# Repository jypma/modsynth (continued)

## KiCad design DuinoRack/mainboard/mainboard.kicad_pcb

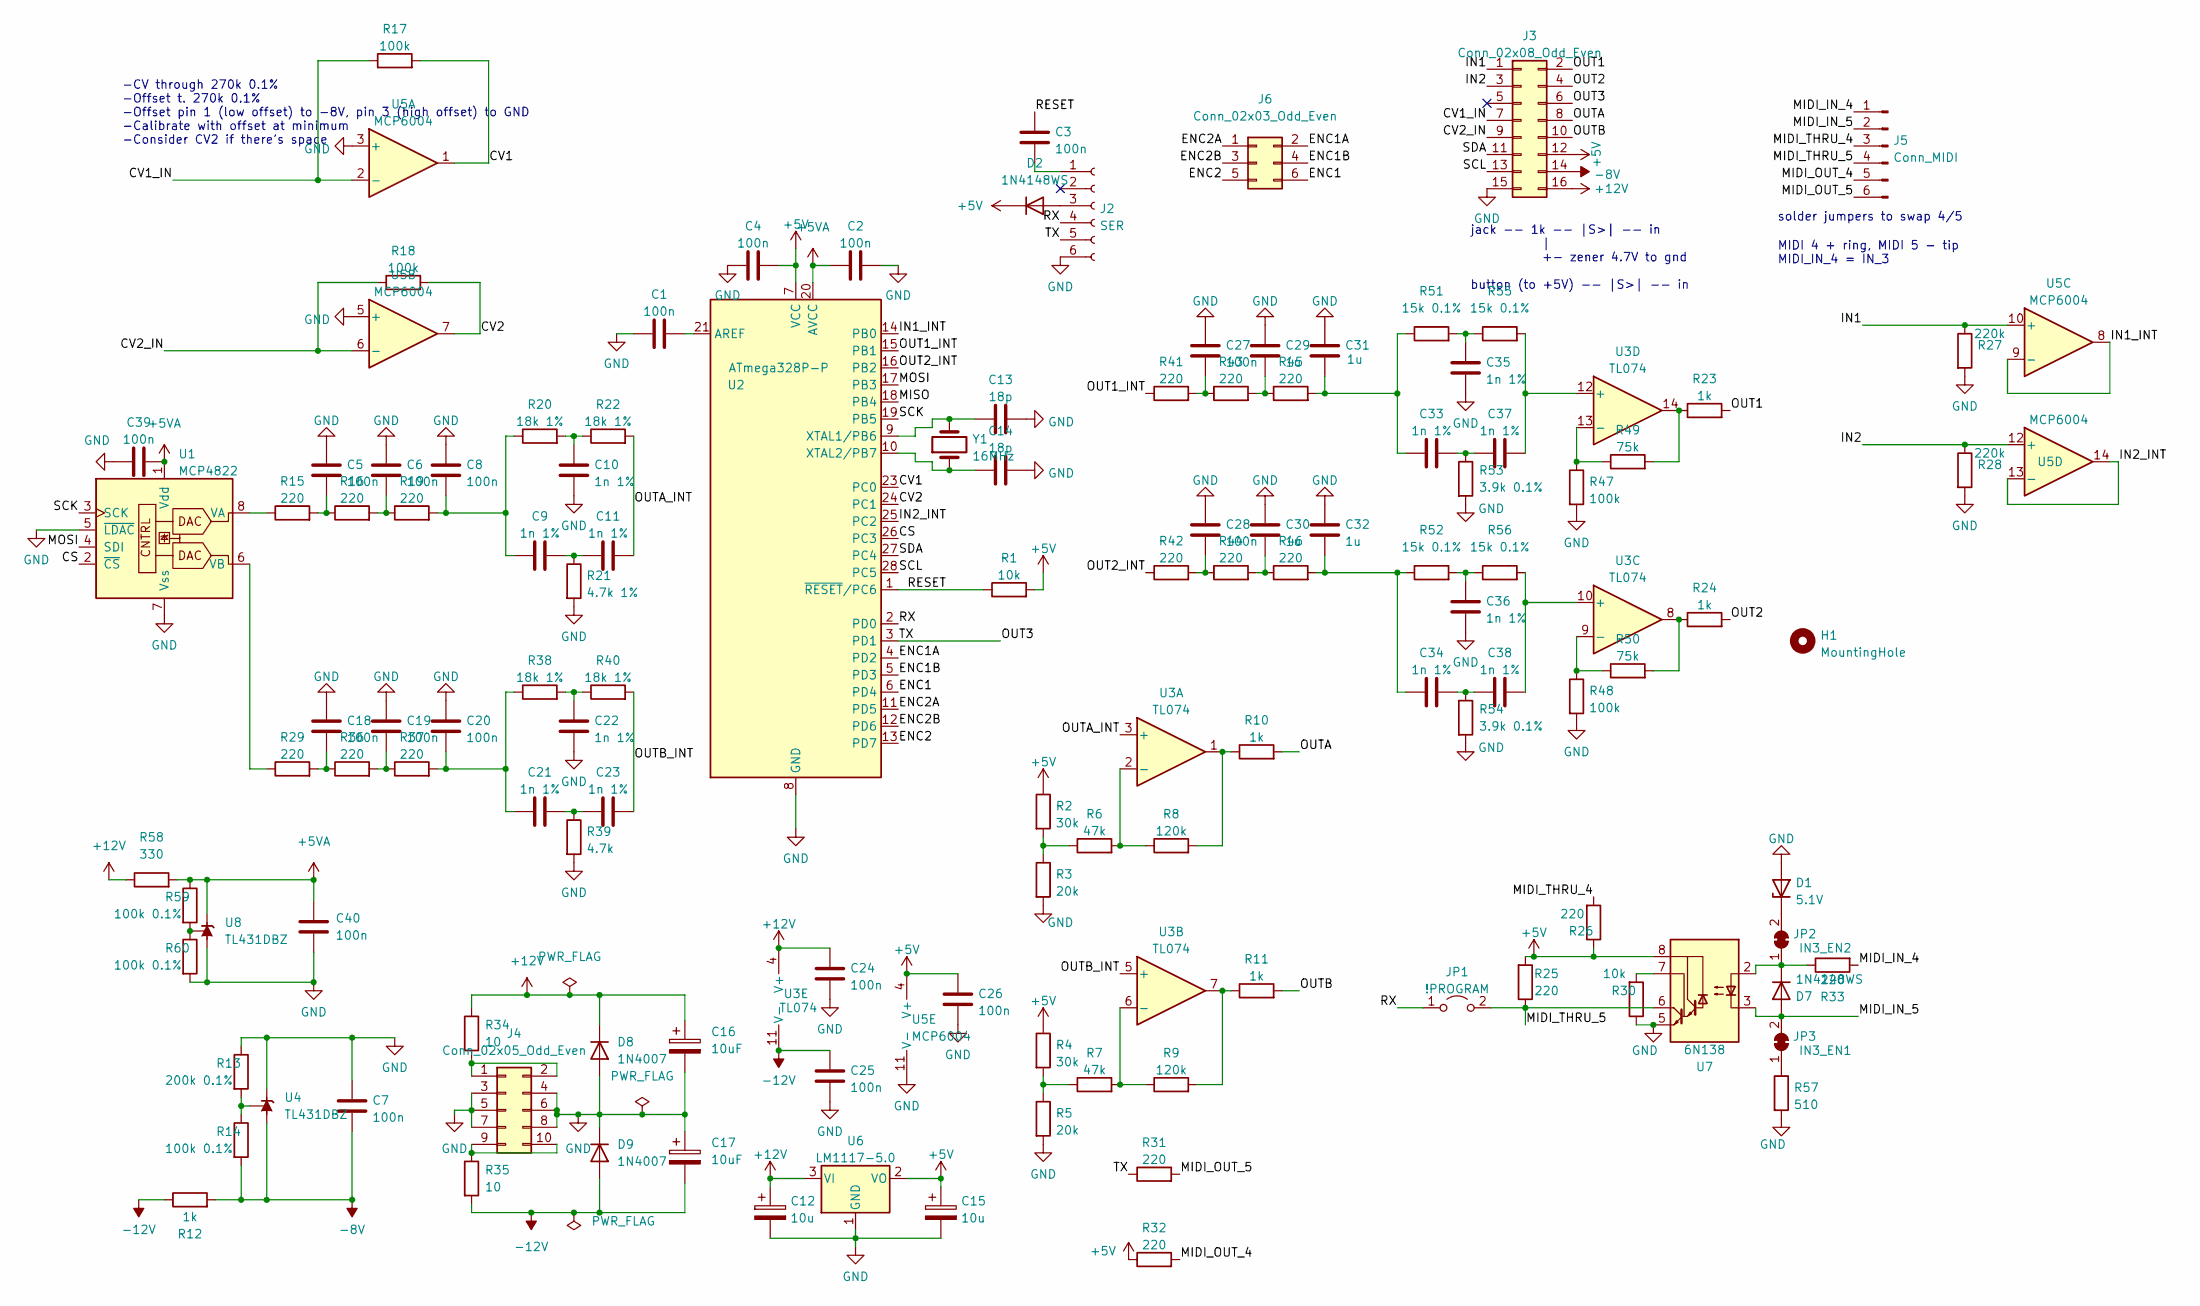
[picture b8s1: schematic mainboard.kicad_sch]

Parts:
C1, C2, C3, C4, C5, C6, C7, C8, C18, C19, C20, C24, C25, C26, C27, C28, C39, C40: 100n; C_0603_1608Metric_Pad1.08x0.95mm_HandSolder
C9, C10, C11, C21, C22, C23, C33, C34, C35, C36, C37, C38: 1n 1%; C_0603_1608Metric_Pad1.08x0.95mm_HandSolder
C12, C15: 10u; C_0603_1608Metric_Pad1.08x0.95mm_HandSolder
C13, C14: 18p; C_0603_1608Metric_Pad1.08x0.95mm_HandSolder
C16, C17: 10uF; CP_Radial_D5.0mm_P2.50mm
C29, C30, C31, C32: 1u; C_0603_1608Metric_Pad1.08x0.95mm_HandSolder
D1: 5.1V; D_DO-35_SOD27_P2.54mm_Vertical_AnodeUp
D2, D7: 1N4148WS; D_SOD-323_HandSoldering
D8, D9: 1N4007; D_DO-41_SOD81_P7.62mm_Horizontal
H1: MountingHole; MountingHole_3.2mm_M3_DIN965
J2: SER; PinHeader_1x06_P2.54mm_Vertical
J3: Conn_02x08_Odd_Even; PinHeader_2x08_P2.54mm_Vertical
J4: Conn_02x05_Odd_Even; PinHeader_2x05_P2.54mm_Vertical
J5: Conn_MIDI; PinHeader_1x06_P2.54mm_Vertical
J6: Conn_02x03_Odd_Even; PinHeader_2x03_P2.54mm_Vertical
JP1: !PROGRAM; PinHeader_1x02_P2.54mm_Vertical
JP2: IN3_EN2; SolderJumper-2_P1.3mm_Bridged_RoundedPad1.0x1.5mm
JP3: IN3_EN1; SolderJumper-2_P1.3mm_Bridged_RoundedPad1.0x1.5mm
R1, R30: 10k; R_0603_1608Metric_Pad0.98x0.95mm_HandSolder
R2, R4: 30k; R_0603_1608Metric_Pad0.98x0.95mm_HandSolder
R3, R5: 20k; R_0603_1608Metric_Pad0.98x0.95mm_HandSolder
R6, R7: 47k; R_0603_1608Metric_Pad0.98x0.95mm_HandSolder
R8, R9: 120k; R_0603_1608Metric_Pad0.98x0.95mm_HandSolder
R10, R11, R12, R23, R24: 1k; R_0603_1608Metric_Pad0.98x0.95mm_HandSolder
R13: 200k 0.1%; R_0603_1608Metric_Pad0.98x0.95mm_HandSolder
R14, R59, R60: 100k 0.1%; R_0603_1608Metric_Pad0.98x0.95mm_HandSolder
R15, R16, R19, R25, R26, R29, R31, R32, R33, R36, R37, R41, R42, R43, R44, R45, R46: 220; R_0603_1608Metric_Pad0.98x0.95mm_HandSolder
R17, R18, R47, R48: 100k; R_0603_1608Metric_Pad0.98x0.95mm_HandSolder
R20, R22, R38, R40: 18k 1%; R_0603_1608Metric_Pad0.98x0.95mm_HandSolder
R21: 4.7k 1%; R_0603_1608Metric_Pad0.98x0.95mm_HandSolder
R27, R28: 220k; R_0603_1608Metric_Pad0.98x0.95mm_HandSolder
R34, R35: 10; R_0603_1608Metric_Pad0.98x0.95mm_HandSolder
R39: 4.7k; R_0603_1608Metric_Pad0.98x0.95mm_HandSolder
R49, R50: 75k; R_0603_1608Metric_Pad0.98x0.95mm_HandSolder
R51, R52, R55, R56: 15k 0.1%; R_0603_1608Metric_Pad0.98x0.95mm_HandSolder
R53, R54: 3.9k 0.1%; R_0603_1608Metric_Pad0.98x0.95mm_HandSolder
R57: 510; R_0603_1608Metric_Pad0.98x0.95mm_HandSolder
R58: 330; R_0603_1608Metric_Pad0.98x0.95mm_HandSolder
U1: MCP4822; DIP-8_W7.62mm_Socket
U2: ATmega328P-P; DIP-28_W7.62mm_Socket
U3: TL074; SO-14_3.9x8.65mm_P1.27mm
U4, U8: TL431DBZ; SOT-23
U5: MCP6004; SO-14_3.9x8.65mm_P1.27mm
U6: LM1117-5.0; SOT-223
U7: 6N138; DIP-8_W7.62mm_Socket
Y1: 16MHz; Crystal_HC18-U_Vertical

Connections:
+5V: C4.2, C15.1, C26.1, D2.1 (K), J3.12, R1.2, R2.1, R4.1, R25.2, R26.1, R32.1, U2.7 (VCC), U5.4 (V+), U6.2 (VO), U7.8 (VCC)
+5VA: C2.1, C39.2, C40.1, R58.2, R59.1, U1.1 (Vdd), U2.20 (AVCC), U8.1 (K)
+12V: C12.1, C16.1, C24.1, D8.1 (K), J3.16, R34.1, R58.1, U3.4 (V+), U6.3 (VI)
-8V: C7.2, J3.14, R12.2, R14.2, U4.3 (A)
-12V: C17.2, C25.1, D9.2 (A), R12.1, R35.2, U3.11 (V-)
/CS: U1.2 (~CS), U2.26 (PC3)
/CV1: R17.2, U2.23 (PC0), U5.1
/CV1_IN: J3.7, R17.1, U5.2 (-)
/CV2: R18.2, U2.24 (PC1), U5.7
/CV2_IN: J3.9, R18.1, U5.6 (-)
/ENC1: J6.6, U2.6 (PD4)
/ENC1A: J6.2, U2.4 (PD2)
/ENC1B: J6.4, U2.5 (PD3)
/ENC2: J6.5, U2.13 (PD7)
/ENC2A: J6.1, U2.11 (PD5)
/ENC2B: J6.3, U2.12 (PD6)
/IN1: J3.1, R27.1, U5.10 (+)
/IN1_INT: U2.14 (PB0), U5.8, U5.9 (-)
/IN2: J3.3, R28.1, U5.12 (+)
/IN2_INT: U2.25 (PC2), U5.13 (-), U5.14
/MIDI_IN_4: J5.1, R33.2
/MIDI_IN_5: D7.2 (A), J5.2, JP3.2 (B), U7.3 (C2)
/MIDI_OUT_4: J5.5, R32.2
/MIDI_OUT_5: J5.6, R31.2
/MIDI_THRU_4: J5.3, R26.2
/MIDI_THRU_5: J5.4, JP1.2 (B), R25.1, U7.6 (VO2)
/MISO: U2.18 (PB4)
/MOSI: U1.4 (SDI), U2.17 (PB3)
/OUT1: J3.2, R23.2
/OUT1_INT: R41.1, U2.15 (PB1)
/OUT2: J3.4, R24.2
/OUT2_INT: R42.1, U2.16 (PB2)
/OUT3: J2.5, J3.6, R31.1, U2.3 (PD1)
/OUTA: J3.8, R10.2
/OUTA_INT: C11.2, R22.2, U3.3 (+)
/OUTB: J3.10, R11.2
/OUTB_INT: C23.2, R40.2, U3.5 (+)
/RESET: C3.1, R1.1, U2.1 (~RESET/PC6)
/RX: J2.4, JP1.1 (A), U2.2 (PD0)
/SCK: U1.3 (SCK), U2.19 (PB5)
/SCL: J3.13, U2.28 (PC5)
/SDA: J3.11, U2.27 (PC4)
GND: C1.1, C2.2, C4.1, C5.1, C6.1, C7.1, C8.1, C10.2, C12.2, C13.2, C14.2, C15.2, C16.2, C17.1, C18.1, C19.1, C20.1, C22.2, C24.2, C25.2, C26.2, C27.1, C28.1, C29.1, C30.1, C31.1, C32.1, C35.2, C36.2, C39.1, C40.2, D1.2 (A), D8.2 (A), D9.1 (K), J2.6, J3.15, J4.3, J4.4, J4.5, J4.6, J4.7, J4.8, R3.2, R5.2, R13.1, R21.2, R27.2, R28.2, R30.1, R39.2, R47.2, R48.2, R53.2, R54.2, R57.2, R60.2, U1.5 (~LDAC), U1.7 (Vss), U2.8 (GND), U2.22 (GND), U4.1 (K), U5.3 (+), U5.5 (+), U5.11 (V-), U6.1 (GND), U7.5 (GND), U8.3 (A)
unnamed: C1.2, U2.21 (AREF)
unnamed: C3.2, J2.1
unnamed: C5.2, R15.2, R16.1
unnamed: C6.2, R16.2, R19.1
unnamed: C8.2, C9.1, R19.2, R20.1
unnamed: C10.1, R20.2, R22.1
unnamed: C9.2, C11.1, R21.1
unnamed: C13.1, U2.9 (XTAL1/PB6), Y1.2
unnamed: C14.1, U2.10 (XTAL2/PB7), Y1.1
unnamed: C18.2, R29.2, R36.1
unnamed: C19.2, R36.2, R37.1
unnamed: C20.2, C21.1, R37.2, R38.1
unnamed: C21.2, C23.1, R39.1
unnamed: C22.1, R38.2, R40.1
unnamed: C27.2, R41.2, R43.1
unnamed: C28.2, R42.2, R44.1
unnamed: C29.2, R43.2, R45.1
unnamed: C30.2, R44.2, R46.1
unnamed: C31.2, C33.1, R45.2, R51.1
unnamed: C32.2, C34.1, R46.2, R52.1
unnamed: C33.2, C37.1, R53.1
unnamed: C34.2, C38.1, R54.1
unnamed: C35.1, R51.2, R55.1
unnamed: C36.1, R52.2, R56.1
unnamed: C37.2, R55.2, U3.12 (+)
unnamed: C38.2, R56.2, U3.10 (+)
unnamed: D1.1 (K), JP2.2 (B)
unnamed: D7.1 (K), JP2.1 (A), R33.1, U7.2 (C1)
unnamed: D2.2 (A), J2.3
unnamed: J4.1, J4.2, R34.2
unnamed: J4.9, J4.10, R35.1
unnamed: JP3.1 (A), R57.1
unnamed: R2.2, R3.1, R6.1
unnamed: R4.2, R5.1, R7.1
unnamed: R6.2, R8.1, U3.2 (-)
unnamed: R7.2, R9.1, U3.6 (-)
unnamed: R8.2, R10.1, U3.1
unnamed: R9.2, R11.1, U3.7
unnamed: R13.2, R14.1, U4.2 (REF)
unnamed: R15.1, U1.8 (VA)
unnamed: R23.1, R49.2, U3.14
unnamed: R24.1, R50.2, U3.8
unnamed: R29.1, U1.6 (VB)
unnamed: R30.2, U7.7 (VO1)
unnamed: R47.1, R49.1, U3.13 (-)
unnamed: R48.1, R50.1, U3.9 (-)
unnamed: R59.2, R60.1, U8.2 (REF)

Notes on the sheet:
solder jumpers to swap 4/5
jack -- 1k -- |S>| -- in | +- zener 4.7V to gnd button (to +5V) -- |S>| -- in
-CV through 270k 0.1% -Offset t. 270k 0.1% -Offset pin 1 (low offset) to -8V, pin 3 (high offset) to GND -Calibrate with offset at minimum -Consider CV2 if there's space
MIDI 4 + ring, MIDI 5 - tip MIDI_IN_4 = IN_3

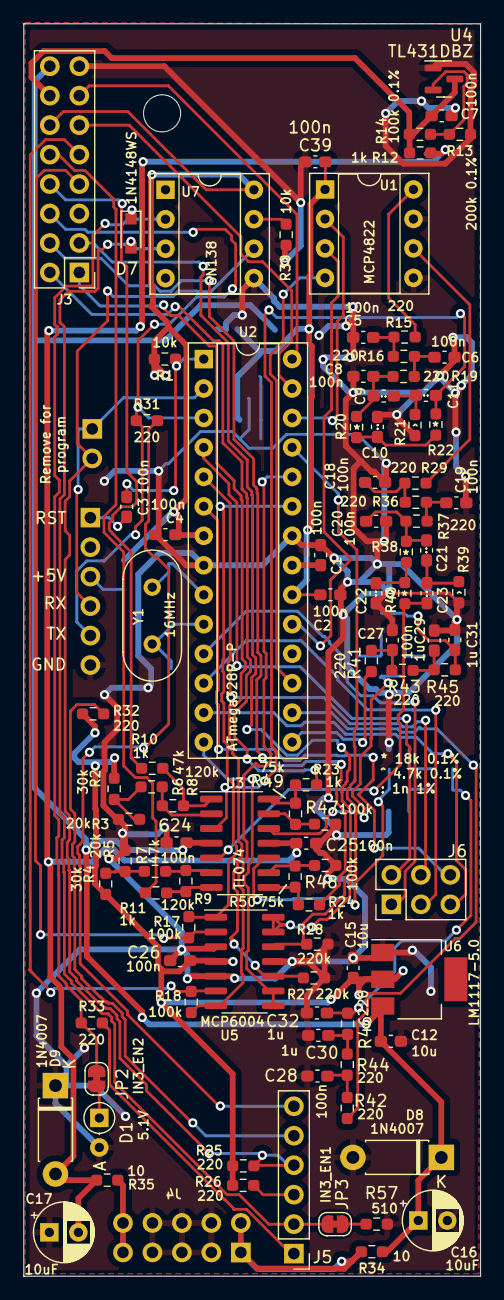
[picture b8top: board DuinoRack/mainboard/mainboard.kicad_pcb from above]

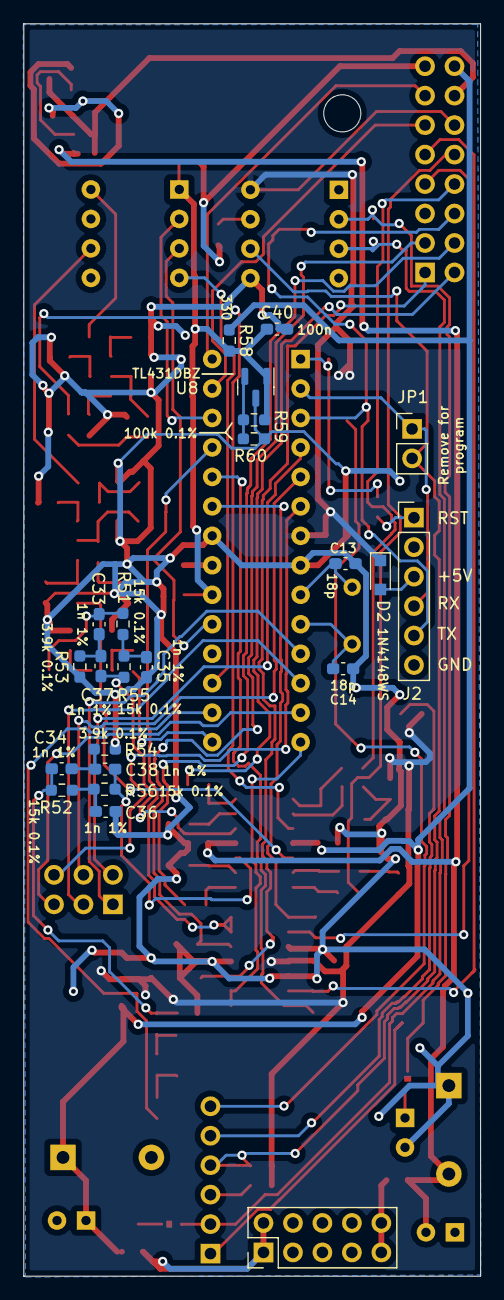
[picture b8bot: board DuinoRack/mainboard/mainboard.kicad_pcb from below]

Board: 2 copper layers, 39.4 x 107.9 mm, 123 parts (23 on the bottom side), 89 nets.

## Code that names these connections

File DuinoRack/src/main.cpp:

#include "Arduino.h"
#include "MCP_DAC.h"
#include <lcdgfx.h>
#include <Versatile_RotaryEncoder.h>
#include "Module.h"
#include "OutputBuf.h"
#include "FuncGen.h"
#include "Calibrate.h"
#include "ADSR.hpp"
#include "IO.h"
#include "LFO.hpp"
#include "Quantize.h"
#include "MIDIMod.h"
#include "canvas/canvas.h"
#include "pins_arduino.h"
#include "Storage.hpp"
#include "Debug.hpp"
#include "Random.hpp"
#include "Sequencer.hpp"

//#define TIMING

// display: 300 bytes RAM

Module currentMod = LFO::module;//FuncGen::module;
uint8_t currentModIdx = 3;

uint8_t shownModIdx = currentModIdx;
uint8_t currentControlIdx = 0;

// Encoder 1 is "Select"
auto encoder1 = Versatile_RotaryEncoder(2,3,4); // PD2, PD3, PD4
// Encoder 2 is "Adjust"
auto encoder2 = Versatile_RotaryEncoder(5,6,7); // PD5, PD6, PD7

OutputBuf::Buffer a, b;
OutputBuf::Buffer *current = &b;

DisplaySSD1306_128x64_I2C display(-1);

MCP4821 MCP;
uint16_t bufferCount;
uint32_t lastTime = 0;
uint8_t oldOverruns = 0;

void fillBuffer() {
  if (OutputBuf::needNextBuffer()) {
    current = (current == &a) ? &b : &a;
    bufferCount++;
#ifdef TIMING
    PORTD |= (1 << 3);
#endif
    currentMod.fillBuffer(*current);  // On arduino boot: ~500us
#ifdef TIMING
    PORTD &= ~(1 << 3);
#endif
    OutputBuf::setNextBuffer(current);
  } else if (encoder1.ReadEncoder()) {
    debugSerial("E1");
  } else if (encoder2.ReadEncoder()) {
    debugSerial("E2");
  } else {
    IO::readIfNeeded();
  }
}

ISR(TIMER2_COMPA_vect) {
#ifdef TIMING
  PORTD |= (1 << 2);
#endif
  OutputBuf::advance();
#ifdef TIMING
  PORTD &= ~(1 << 2);
#endif
}

void setModuleIdx(int8_t idx) {
  currentMod.stop();
  currentControlIdx = 0;
  currentModIdx = idx % MODULE_COUNT;
  debugSerial(currentModIdx);
  switch(currentModIdx) {
    case 0: currentMod = FuncGen::module; break;
    case 1: currentMod = ADSR::module; break;
    case 2: currentMod = MIDIMod::module; break;
    case 3: currentMod = LFO::module; break;
    case 4: currentMod = Quantize::module; break;
    case 5: currentMod = Sequencer::module; break;
    default: currentMod = Calibrate::module;
  }
  // Startup trigger
  currentMod.start();
  currentMod.adjust(0);
}

void drawText(uint8_t x, uint8_t y, const char *s) {
  if (!*s) return;
  display.setTextCursor(x, y);
  while (*s) {
    fillBuffer();
    display.printChar(*s);
    fillBuffer();
    s++;
  }
}

void drawSelected(uint8_t x, uint8_t y, uint8_t control) {
  drawChar(x, y, (currentControlIdx == control) ? '>' : ' ');
}

void drawChar(uint8_t x, uint8_t y, char ch) {
  if (!ch) return;
  display.setTextCursor(x, y);
  fillBuffer();
  display.printChar(ch);
}

void clearChars(uint8_t x, uint8_t y, uint8_t count) {
  display.setTextCursor(x, y);
  while (count > 0) {
    fillBuffer();
    display.printChar(' ');
    count--;
  }
}

void drawDecimal(uint8_t x, uint8_t y, int16_t value) {
  char str[7];
  itoa(value, str, 10);
  drawText(x, y, str);
  drawTextPgm(x + strlen(str) * 6, y, clear);
}

void drawDecimal(uint8_t x, uint8_t y, int16_t value, uint8_t expectedChars) {
  char str[7];
  itoa(value, str, 10);
  drawText(x, y, str);
  uint8_t len = strlen(str);
  clearChars(x + len * 6, y, (expectedChars > len) ? expectedChars - len : 0);
}

void drawDecimal(uint8_t x, uint8_t y, int16_t value, char suffix, uint8_t expectedChars) {
  char str[7];
  itoa(value, str, 10);
  drawText(x, y, str);
  uint8_t len = strlen(str);
  drawChar(x + len * 6, y, suffix);
  len++;
  clearChars(x + len * 6, y, (expectedChars > len) ? expectedChars - len : 0);
}

void drawTextPgm(uint8_t x, uint8_t y, const char *s) {
  uint8_t ch = pgm_read_byte(s);
  if (!ch) return;
  display.setTextCursor(x, y);
  while (ch) {
    fillBuffer();
    display.printChar(ch);
    fillBuffer();
    s++;
    ch = pgm_read_byte(s);
  }
}

bool showLongPress = false;
void showModule() {
  if (shownModIdx != currentModIdx) {
    display.fill(0x00);
  }
  if (currentControlIdx == 0) {
    drawText(0, 8, ">");
  } else {
    drawText(0, 8, " ");
  }
  drawText(120, 8, showLongPress ? "S" : " ");
  drawTextPgm(8, 8, currentMod.name);
  shownModIdx = currentModIdx;
}

// Encoder 2 is "Adjust"
void handleEncoder2Rotate(int8_t rotation) {
  static uint32_t prevTime = 0;
  static uint8_t accel = 1;
  auto time = millis();
  uint8_t maxAccel = (currentControlIdx == 0) ? 1 : 16;
  if ((time - prevTime < 100) && (accel < maxAccel)) {
    accel <<= 1;
  } else {
    accel = 1;
  }
  prevTime = time;

  // Don't draw to screen here, as this may be called in the middle of drawing to the screen!
  if (currentControlIdx == 0) {
    setModuleIdx(applyDelta<uint8_t>(currentModIdx, rotation, 0, MODULE_COUNT - 1));
  } else {
    // TODO control acceleration differently for different controls
    rotation *= accel;
    currentMod.adjust(rotation);
  }
}

void handleEncoder2PressRelease() {
  showLongPress = false;
  if (currentMod.adjustPressed != NULL) {
    currentMod.adjustPressed();
  }
}

// Encoder 1 is "Select"
void handleEncoder1Rotate(int8_t rotation) {
  static uint32_t prevTime = 0;
  static uint8_t accel = 1;
  auto time = millis();
  uint8_t maxAccel = 4;
  if ((time - prevTime < 100) && (accel < maxAccel)) {
    accel <<= 1;
  } else {
    accel = 1;
  }
  prevTime = time;
  rotation *= accel;

  // Don't draw to screen here, as this may be called in the middle of drawing to the screen!
  currentControlIdx = (currentControlIdx + (currentMod.controlCount + 1) + rotation) % (currentMod.controlCount + 1);
}


void handleEncoder1LongPress() {
  showLongPress = true;
}

void handleEncoder1LongPressRelease() {
  // TODO: Show a menu here to load/save preset slots. For now, we just save in preset 0.
  Storage::savePreset(0);
  showLongPress = false;
}

void displayExtraInit() {
  // Copied from lcdgfx' own avr_twi implementation, but they forget(?) to call it
#define SSD1306_TWI_FREQ 400000

  DDRC &= ~(1 << PINC4);
  PORTC |= (1 << PINC4);
  DDRC &= ~(1 << PINC5);
  PORTC |= (1 << PINC5);

  TWSR = 0;

  TWBR = ((F_CPU / SSD1306_TWI_FREQ) - 16) / 2 / (1); // Always use prescaler 1 (TWSR 0x00)
  TWCR = (1 << TWEN) | (1 << TWEA);
}

void setup() {
#ifdef DEBUG_SERIAL
  Serial.begin(31250);
  debugSerial("DuinoRack");
  Serial.flush();
#else
  // TODO move to IO::setup
  pinMode(1, OUTPUT); // TX (PD1) is Gate 3
#endif

  IO::setup();
  IO::setGate3Out(true);
  Storage::load();

  // We need input pull-ups for our encoder inputs
  pinMode(2, INPUT_PULLUP);
  pinMode(3, INPUT_PULLUP);
  pinMode(5, INPUT_PULLUP);
  pinMode(6, INPUT_PULLUP);

  Random::addSeed(uint16_t(IO::getCV1In()));
  Random::addSeed(uint16_t(IO::getCV2In()));
  Random::addSeed(TCNT0);
  Random::addSeed(TCNT1);
  Random::addSeed(TCNT2);

  currentMod.start();
  encoder1.setHandleRotate(handleEncoder1Rotate);
  encoder1.setHandleLongPress(handleEncoder1LongPress);
  encoder1.setHandleLongPressRelease(handleEncoder1LongPressRelease);
  encoder2.setHandleRotate(handleEncoder2Rotate);
  encoder2.setHandlePressRelease(handleEncoder2PressRelease);

  displayExtraInit();
  display.begin();
  display.fill(0x00);
  display.setFixedFont(ssd1306xled_font6x8);
  showModule();
  debugSerial("Display ready.");

  // fill initial buffer
  fillBuffer();

  MCP.begin(PIN_A3);  // select pin = 17, PC3 / A3 / D17
  MCP.fastWriteA(0);
  MCP.fastWriteB(0);

#ifdef TIMING
  pinMode(2, OUTPUT);
  pinMode(3, OUTPUT);
  pinMode(5, OUTPUT);
  pinMode(6, OUTPUT);
#endif

  // Set up timer2 for maximum speed
  TCCR2A = 0;// set entire TCCR2A register to 0
  TCCR2B = 0;// same for TCCR2B
  TCNT2  = 0;//initialize counter value to 0
  // set compare match register to sample rate (def. 12000)
  constexpr uint8_t ovfValue = uint32_t(F_CPU) / 32 / SAMPLERATE;
  OCR2A = ovfValue;
  // turn on CTC mode
  TCCR2A |= (1 << WGM21);
  // 8 prescaler
  //TCCR2B = (1 << CS21);
  // 32 prescaler
  TCCR2B = (1 << CS21) | (1 << CS20);
  // enable timer compare interrupt
  TIMSK2 |= (1 << OCIE2A);
  IO::setGate3Out(false);
}

void loop() {
  fillBuffer();
  uint32_t now = micros();
  fillBuffer();

  if (OutputBuf::overruns != oldOverruns) {
    oldOverruns = OutputBuf::overruns;
    // TODO show XRun on screen
    debugSerial("Xrun! ");
    debugSerial(oldOverruns);
  }

  if (now - lastTime > 100000)
  {
    lastTime = now;
    //debugSerial(bufferCount); // bufferCount: ~36 per 100ms, for SAMPLERATE 12000
    bufferCount = 0;
    //debugSerial(OutputBuf::samples); // samples: ~600 per 100ms, or 6000 per second, for SAMPLERATE 12000
    // SAMPLERATE 8000 -> 400 samples per 10ms. PRescaler wrong?
    OutputBuf::samples = 0;
#ifdef TIMING
    PORTD |= (1 << 5);
#endif
    showModule(); // takes 10ms
#ifdef TIMING
    PORTD &= ~(1 << 5);
#endif
    fillBuffer();
#ifdef TIMING
    PORTD |= (1 << 6);
#endif
    currentMod.draw(); // For LFO: takes 50ms on 2000Hz. 100ms on 4000Hz.
#ifdef TIMING
    PORTD &= ~(1 << 6);
#endif
  }
}

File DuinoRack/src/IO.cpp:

#include <Arduino.h>
#include <avr/sfr_defs.h>
#include <mozzi_fixmath.h>
#include "IO.h"
#include "Module.h"
#include "Storage.hpp"

namespace IO {
uint16_t cvIn1 = 0;
uint16_t cvIn2 = 0;
bool readingCv1 = true;

int16_t cvIn1_0V = 567;
int16_t cvIn1_4V = 269;
int16_t cvIn2_0V = 569;
int16_t cvIn2_4V = 270;

int16_t cvOut1_0V = 1335;
int16_t cvOut1_4V = 2659;
int16_t cvOut2_0V = 1328;
int16_t cvOut2_4V = 2653;

int16_t gate1_0V = 377;
int16_t gate1_4V = 720;
int16_t gate2_0V = 379;
int16_t gate2_4V = 721;

Q15n16 cvOut1Factor = 0;
Q15n16 cvOut2Factor = 0;
Q15n16 gate1Factor = 0;
Q15n16 gate2Factor = 0;

int16_t getcvOut1_0V() { return cvOut1_0V; }
int16_t getcvOut1_4V() { return cvOut1_4V; }
int16_t getcvOut2_0V() { return cvOut2_0V; }
int16_t getcvOut2_4V() { return cvOut2_4V; }

int16_t getGate1_0V() { return gate1_0V; }
int16_t getGate1_4V() { return gate1_4V; }
int16_t getGate2_0V() { return gate2_0V; }
int16_t getGate2_4V() { return gate2_4V; }

void recalibrate() {
  cvOut1Factor = Q15n0_to_Q15n16(cvOut1_4V - cvOut1_0V) / 1000 / 4;
  cvOut2Factor = Q15n0_to_Q15n16(cvOut2_4V - cvOut2_0V) / 1000 / 4;
  gate1Factor = Q15n0_to_Q15n16(gate1_4V - gate1_0V) / 1000 / 4;
  gate2Factor = Q15n0_to_Q15n16(gate2_4V - gate2_0V) / 1000 / 4;
}

void calibratePWMPeriod(int16_t delta) {
  ICR1 = constrain(ICR1 + delta, 800, uint32_t(F_CPU) / SAMPLERATE);
}

uint16_t getPWMPeriod() {
  return ICR1;
}

void calibrateCVOut1_0V(int16_t delta) {
  cvOut1_0V = constrain(cvOut1_0V + delta, 0, cvOut1_4V);
  recalibrate();
}

void calibrateCVOut1_4V(int16_t delta) {
  cvOut1_4V = constrain(cvOut1_4V + delta, cvOut1_0V, 4095);
  recalibrate();
}

void calibrateCVOut2_0V(int16_t delta) {
  cvOut2_0V = constrain(cvOut2_0V + delta, 0, cvOut2_4V);
  recalibrate();
}

void calibrateCVOut2_4V(int16_t delta) {
  cvOut2_4V = constrain(cvOut2_4V + delta, cvOut2_0V, 4095);
  recalibrate();
}

void calibrateGate1_0V(int16_t delta) {
  gate1_0V = constrain(gate1_0V + delta, 0, gate1_4V);
  recalibrate();
}

void calibrateGate1_4V(int16_t delta) {
  gate1_4V = constrain(gate1_4V + delta, gate1_0V, 1023);
  recalibrate();
}

void calibrateGate2_0V(int16_t delta) {
  gate2_0V = constrain(gate2_0V + delta, 0, gate2_4V);
  recalibrate();
}

void calibrateGate2_4V(int16_t delta) {
  gate2_4V = constrain(gate2_4V + delta, gate2_0V, 1023);
  recalibrate();
}

int16_t getCV1In() {
  return (int32_t(cvIn1_0V) - cvIn1) * 4000 / (cvIn1_0V - cvIn1_4V);
}

int16_t getCV2In() {
  return (int32_t(cvIn2_0V) - cvIn2) * 4000 / (cvIn2_0V - cvIn2_4V);
}

uint16_t calcCV1Out(int16_t mV) {
  // TODO compare generated assembly to https://github.com/rekka/avrmultiplication/blob/master/mult32x16.h
  return Q15n16_to_Q15n0(cvOut1Factor * mV) + cvOut1_0V;
}

uint16_t calcCV2Out(int16_t mV) {
  return Q15n16_to_Q15n0(cvOut2Factor * mV) + cvOut2_0V;
}

uint16_t calcGate1Out(int16_t mV) {
  return Q15n16_to_Q15n0(gate1Factor * mV) + gate1_0V;
}

uint16_t calcGate2Out(int16_t mV) {
  return Q15n16_to_Q15n0(gate2Factor * mV) + gate2_0V;
}

bool getGate1In() {
  return (PINB & (1 << 0)) != 0;
}

bool getGate2In() {
  return (PINC & (1 << 2)) != 0;
}

bool getGate3In() {
  // This is behind the MIDI in optocoupler, hence inverted.
  return (PIND & (1 << 0)) == 0;
}

void setGate1Out(bool on) {
  // PB1, D9
  if (on) {
    PORTB |= (1 << 1);
  } else {
    PORTB &= ~(1 << 1);
  }
}

void setGate2Out(uint8_t on) {
  // PB2, D10
  if (on) {
    PORTB |= (1 << 2);
  } else {
    PORTB &= ~(1 << 2);
  }
}

void setup() {
  recalibrate();

  // Select Vref=AVcc
  ADMUX = _BV(REFS0);
  //set prescaller to 128 (at 16MHz, is 125kHz)and enable ADC
  ADCSRA |= _BV(ADPS2) | _BV(ADPS1) | _BV(ADPS0) | _BV(ADEN);
  // Start with channel 0 (CV in 1)
  readingCv1 = true;
  ADMUX = (ADMUX & 0xF0) | (0 & 0x0F);
  //single conversion mode
  ADCSRA |= _BV(ADSC);

  pinMode(8, INPUT); // PB0, Gate IN 1
  pinMode(16, INPUT); // PC2, Gate IN 2

  pinMode(9, OUTPUT); // PB1, Gate OUT 1
  pinMode(10, OUTPUT); // PB2, Gate OUT 2

  // Set up timer 1 for maximum speed
  TCCR1A = 0;
  TCCR1B = 0;
  TCNT1  = 0;//initialize counter value to 0
  constexpr uint16_t ovfValue = 1024;
  ICR1 = ovfValue;
  // Waveform generation mode 14: Fast PWM, TOP is ICR1,
  // and Timer1 clock source is CPU / 1 (16MHz).
  TCCR1A |= _BV(WGM11);
  TCCR1B |= _BV(WGM12) | _BV(WGM13) | _BV(CS10);

  // Non-inverting fast PWM mode
  TCCR1A |= _BV(COM1A1);
  setGate1Out(calcGate1Out(0));
  // Non-inverting fast PWM mode
  TCCR1A |= _BV(COM1B1);
  setGate2Out(calcGate2Out(0));
}

void readIfNeeded() {
  if ((ADCSRA & (1<<ADSC)) == 0) {
    if (readingCv1) {
      cvIn1 = ADC;
      readingCv1 = false;
      ADMUX = (ADMUX & 0xF0) | (1 & 0x0F);
    } else {
      cvIn2 = ADC;
      readingCv1 = true;
      ADMUX = (ADMUX & 0xF0) | (0 & 0x0F);
    }
    //single conversion mode
    ADCSRA |= (1<<ADSC);
  }
}

constexpr uint16_t addr = 4; // Calibration is stored immediately after magic bytes
void saveCalibration() {
  Storage::write(addr, cvIn1_0V);
  Storage::write(addr + 2, cvIn1_4V);
  Storage::write(addr + 4, cvIn2_0V);
  Storage::write(addr + 6, cvIn2_4V);

  Storage::write(addr + 8, cvOut1_0V);
  Storage::write(addr + 10, cvOut1_4V);
  Storage::write(addr + 12, cvOut2_0V);
  Storage::write(addr + 14, cvOut2_4V);

  Storage::write(addr + 16, gate1_0V);
  Storage::write(addr + 18, gate1_4V);
  Storage::write(addr + 20, gate2_0V);
  Storage::write(addr + 22, gate2_4V);
}

void loadCalibration() {
  Storage::read(addr, cvIn1_0V);
  Storage::read(addr + 2, cvIn1_4V);
  Storage::read(addr + 4, cvIn2_0V);
  Storage::read(addr + 6, cvIn2_4V);

  Storage::read(addr + 8, cvOut1_0V);
  Storage::read(addr + 10, cvOut1_4V);
  Storage::read(addr + 12, cvOut2_0V);
  Storage::read(addr + 14, cvOut2_4V);

  Storage::read(addr + 16, gate1_0V);
  Storage::read(addr + 18, gate1_4V);
  Storage::read(addr + 20, gate2_0V);
  Storage::read(addr + 22, gate2_4V);
}
}

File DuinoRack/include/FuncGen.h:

#pragma once

#include <mozzi_midi.h>
#include <mozzi_fixmath.h>
#include "Waves.hpp"

#include "Module.h"
#include "IO.h"
#include "OutputBuf.h"
#include "mozzi_pgmspace.h"

#include <EEPROM.h>

namespace FuncGen {

  // LOOKUP TABLE SINE
  constexpr uint16_t TABLE_SIZE = 256;
  constexpr uint16_t Q_TABLE_SIZE = 64;
  constexpr uint16_t Q3_TABLE_SIZE = 192;

  constexpr uint8_t sinePosScaleBits = 10;
  constexpr uint32_t sinePosScale = 1024;
  constexpr uint32_t sinePosMod = uint32_t(TABLE_SIZE) * sinePosScale;
  constexpr Q16n16 MAX_NOTE = 5242880; // Note 80, ~800Hz
  constexpr Q16n16 MIN_NOTE = 65536; // Note 1

  uint32_t sinePos = 0;
  uint16_t recalc = 0;
  uint32_t increment;
  uint8_t noteIdx = 0;
enum Wave: uint8_t { Sine = 0, Triangle = 1, Saw = 2, Square = 3 };
  Wave wave = Sine;

  const char title[] PROGMEM = "FuncGen   ";
  const char note[] PROGMEM = "Note: ";
  const char wave_t[] PROGMEM = "Wave: ";
  const char sine_t[] PROGMEM = "Sine    ";
  const char triangle_t[] PROGMEM = "Triangle";
  const char square_t[] PROGMEM = "Square  ";
  const char saw_t[] PROGMEM = "Saw     ";

  void draw() {
    drawTextPgm(0, 16, note);
    drawDecimal(40, 16, noteIdx);
    drawTextPgm(16, 24, wave_t);
    switch(currentControlIdx) {
    case 1: drawText(0, 24, ">"); break;
    default: drawText(0, 24, " ");
    }
    switch (wave) {
    case Sine: drawTextPgm(52, 24, sine_t); break;
    case Triangle: drawTextPgm(52, 24, triangle_t); break;
    case Saw: drawTextPgm(52, 24, saw_t); break;
    case Square: drawTextPgm(52, 24, square_t); break;
    }

    drawTextPgm(0, 32, clear);
  }

  void adjust(int8_t d) {
    switch(currentControlIdx) {
    case 1:
      wave = Wave((wave + d + 4) % 4);
      break;
    }
  }

  void start() {
  }

  void stop() {

  }

int16_t getWaveValue() {
  const uint8_t p = sinePos >> sinePosScaleBits;
  switch (wave) {
    case Sine: return Waves::Sine::get(p);
    case Triangle: return Waves::Triangle::get(p);
    case Saw: return Waves::SawDown::get(p);
    case Square: return Waves::Square::get(p);
  }
  return 0;
}

void fillBuffer(OutputBuf::Buffer &buffer) {
    if (recalc == 0) {
      // TODO if this works, refactor getCV1In to return Q16n16 instead for a bit of extra speed?
      int16_t in = IO::getCV1In();
      if (in < 0) {
        in = 0;
      }
      Q16n16 note = (((uint32_t(in) / 1000) << 16) | ((uint32_t(in % 1000) << 16) / 1000)) * 12;
      if (note > MAX_NOTE) {
        note = MAX_NOTE;
      } else if (note < MIN_NOTE) {
        note = MIN_NOTE;
      }
      noteIdx = (note >> 16);
      Q16n16 freq = Q16n16_mtof(note);
      increment = (((((uint32_t(freq) >> 8) * TABLE_SIZE) >> 8) << sinePosScaleBits) ) / SAMPLERATE;
      recalc = 1;
    } else {
      recalc--;
    }

    OutputFrame *buf = buffer.analog;
    for (uint8_t i = 0; i < OUTBUFSIZE; i++) {
      sinePos = (sinePos + increment);
      if (sinePos > sinePosMod) {
        sinePos -= sinePosMod;
      }
      // We don't use calibration for channels 2, 3 and 4. We might remove them from the VCO anyway
      // (better to have a single more fun voice).
      const int16_t rawValue = IO::calcCV1Out(getWaveValue());
      buf->cv1 = rawValue;
      buf->cv2 = rawValue;
      buf->gate1 = rawValue >> 2;
      buf->gate2 = buf->gate1;
      buf++;
    }
  }

void save(uint16_t addr) {
  uint8_t version = 1;
  EEPROM.put(addr, version);
  addr++;
  EEPROM.put(addr, wave);
}

void load(uint16_t addr) {
  uint8_t version;
  EEPROM.get(addr, version);
  if (version != 1) return;
  addr++;
  EEPROM.get(addr, wave);
}

  constexpr Module module = {
    title,
    1,
    &draw,
    &start,
    &stop,
    &adjust,
    &fillBuffer,
    NULL,
    &save,
    &load
  };

} // FuncGen

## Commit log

2022-08-18 Added Ornament and Crime
2022-08-18 Added ADSR
2022-08-18 Added VCO
2022-08-18 Added TuringMachine
2022-08-20 Add dual CVA and update PCB with values
2022-08-20 Update OC faceplace
2022-08-20 Update ioboard
2022-08-20 faceplace
2022-08-22 Main board finished, ready to split up into ioboard
2022-08-22 Created separate gerbers for main and io board
2022-08-22 Add resistors to make pots more center sensitive
    Idea from here:
    https://kassu2000.blogspot.com/2018/04/precision-attenuverter-mixer.html
2022-08-22 Final preparations for board splitup
2022-08-22 Fixed duplicate net names for LEDn
2022-08-23 Initial routing of ioboard
2022-08-25 Add IOBoard with the right knob distance
2022-08-29 Added README and face plate
2022-08-29 Initial kibot export integration
    And small fixes in the ioboard to remove the warnings.
2022-08-29 Few faceplate cleanups to get rid of warnings
2022-08-29 Replace polygon with arc+lines for cutout
    Since pcbdraw from kibot doesn't like plotting polygons on EdgeCuts
2022-08-31 Add electrolytic caps and inrush resistors
2022-08-31 Dual mixer initial mixed mainboard version
2022-08-31 Add missing output connectors to IO board
2022-09-01 Split up into mainboard and ioboard
    And do routing for mainboard
2022-09-01 Routed ioboard, add markings to mainboard
2022-09-02 Add face plate for mixer
2022-09-02 Remove name from face plate
2022-09-05 Touching up of faceplates to make them KiBot export compatible
2022-09-06 Change LM13700 to be SMD since that's the only part available
    In both TME and LCSC.
2022-09-06 Kicost experiment: Add a few manufacturer codes
    Unfortunately, many of the LCSC parts aren't picked up with these
    codes. So we'll so the merged BOM manually for now.
2022-09-06 Remove gerbers
    Use export.sh from now on to generate them. We might put them back from
    a Github job later under /export/.
2022-09-06 Replace TL047P with SMD
    Since that's the only package available from LCSC.
2022-09-06 Align potentiometer packages to standard 3-pin 0.1"
2022-09-06 Align footprints to actual shapes
2022-09-06 Adjusted LM324 to actual SO14 package
2022-09-08 Ornament & Crime faceplate update
    A few tweaks to make it compatible with export, and fix a few DRC warnings.
2022-09-09 Add a SOIC16 to DIP16 adapter
    Since the TuringMachine DAC may only arrive in SOIC package, and I don't
    want to redo the board.
2022-09-09 Add first version of the merged BOM
2022-09-09 Add first exported images and documentation
2022-09-09 Add pots to BOM
2022-09-09 Documentation fixups
2022-09-09 Add IO board to documentation
2022-09-10 Add power distribution board
2022-09-10 BOM updates
2022-09-10 Add USB header to O&C face plate
    Because some of the alternative firmwares provide USB HOST.
    We'll figure out if a diode is enough to power it.
2022-09-10 Update power connector graphics
    To make it clear how 10-pin IDC connector would be placed w.r.t. +12 and -12.
2022-09-11 Add remaining documentation, and rename a few directories
    For consistency.
2022-09-11 Fix typo
    The teensie is 3.x, not 4.x
2022-09-11 Add back of O&C faceplate, and re-export
2022-09-11 Get rid of date in SVG file bodies
    This way, re-running export doesn't generate a diff for schematics/PCBs
    that weren't changed.
2022-09-11 Add missing JPG for O&C faceplate
2022-09-11 Thicken power traces for USB connector
2022-09-13 Add M3 mount for mechanical stability, and update power
    If pots are used that don't have mounting brackets, the faceplate needs
    extra mechanical support at the top. Two M3 screws can support that.
    In addition, bottom silk screen is added for the power connector, since
    it's probably going to be mounted there.
2022-09-13 Add M3 mount for mechanical stability, and update power
    This time for the DualMixer as well, it could do with extra supports
2022-09-13 Split up into separate main and io boards, update power silkscreen
    Power connector silkscreen was updated to make it more obvious that the
    connector is to be mounted on the backside, in the same orientation as
    front silk screen.
2022-09-13 Add M3 mounting holes for mechanical stability
    In case non-threaded potentiometers are used
2022-09-13 Add extra ioboard + mainboard holes securing connection
    So the two boards don't separate after installation.
2022-09-15 Add the Steiner VCF from gerb-ster
    Not included in the BOM yet, we'll do that later.
2022-09-15 Add exported artifacts for documentation
2022-09-15 Document exporting process
2022-09-15 Fix wrong logo on filter face plate
2022-09-16 Also export back silkscreen, and add some missing back silkscreen
2022-11-01 Add initial design for DuinoRack
2022-11-01 Add a few simulation and notes for built modules
2022-11-16 Add initial test firmware for DuinoRack
    Timings and main loop confirmed, ready to add calibration as next step.
2022-11-16 Add a few links to simulations
2022-11-18 Add a working menu system for modules
2022-11-22 Add calibration of incoming ADC values
    Two-value linear calibration for now.
2022-11-23 Add working calibration menu for inputs
2022-11-23 Add working output calibration to menu
2022-11-24 Add CV control to function generator
    And lots of experiments to keep the speed.
2022-11-24 Tweak function generator for more speed
    Gives decent audio now, clear peak at 8kHz so we need some filtering.
2022-11-29 Timing output changes, more precise xrun logging
2022-11-29 Add triangle wave to function generator
2022-11-30 Add a simple ADSR
    Just to test that the input gates are working (they were not).
    Also add a TODO for optimizations of the calibrated output.
2022-12-02 Increase sample rate to 12 kHz
2022-12-02 First draft of DuinoRack main board schematic
2022-12-05 Reduce table size to 256
    To allow potentially faster calculations
2022-12-05 Don't recaulculate CV output all the time
    So we don't xrun
2022-12-06 First version of AS3340 VCO
2022-12-06 Various readme updates
2022-12-07 Add MIDI input module and test hardware
    Were removing gate input 3, since there's no way to handle the inversion.
2022-12-13 Actually run at 12kHz
    The previous manual calculation was a bit off, so we might as well tie
    it to the defined output sample frequency.
2022-12-13 Add programming jumper, fix up MIDI in and THRU
    We need to disconnect midi in during programming, since it will pull up
    RX. Hence the new jumper.
2022-12-15 Move gate outputs to Timer1 ports
    By having the gate outputs connected to Timer1, we can drive them with
    PWM, enabling up for other later use cases. A low-pass filter was added
    in the output stage to accommodate for this.
    We'll keep using normal digital I/O in gate mode, since PWM would be
    too noisy there.
2022-12-15 Update layout with latest pcb changes
2022-12-15 Add -5V regulator so internal zener doesn't heat up
    The internal zener of the AS3340 chip will heat up the chip, causing it
    to take ~45 minutes to create a stable frequency. With an external -5V
    it only takes 15 minutes.
2022-12-21 Calibrate outputs PWM so let's set it up like that
2023-01-03 Add configurable input protection to enable gate IN3
2023-01-03 Add 3rd gate input, and monitor gates during calibrate
2023-01-03 Add a few readmes, and delete backup
2023-01-24 Finish DuinoRack hardware, final touches on AS3340 VCO
2023-01-24 Add a few missing knob designs
2023-03-24 Add calibration routine for AS3340 VCO
2023-03-24 Fix calibration UI to always update the proper voltage
    And only set +8V on the right pin.
2023-03-24 Calibrate to +4V instead of +8V
    Lower voltages are more likely to be needed to be accurate, and it
    better aligns with the incoming CV calibration at 4V.
2023-03-24 Apply 4V calibration to prototype, and limit minimum note on funcgen
2023-03-27 Update calibration for 4V on output gates
    And remove the timing output which messed with gate 1 output.
2023-03-29 Read wave shapes from flash; add LFO module
2023-03-29 Swap encoders (silkscreen 1 is select, 2 is adjust)
2023-03-29 Add tap tempo and sync to LFO
    Also only calculate once per buffer (otherwise the millis() call is too
    slow)
2023-03-29 Added clock multiplier and divisor
2023-03-29 Nicer LFO factor presentation, fix compiler warning
2023-03-29 Add controls for gate output 1 in LFO
2023-03-29 Add fourth channel to LFO outputs
2023-03-30 Add acceleration to encoder adjustments
2023-03-30 Add calibration for new -4V .. +8V range of gate outputs
2023-03-31 Add a quantizer module with some scales
2023-04-01 Add a few more scales, and ability to set root of scale
2023-04-01 Add more scales
2023-04-01 Sort alphabetically
2023-04-02 Calibrate output of LFO and FuncGen
    And make the embedded tables hold voltages (mV), instead of raw DAC
    values.
2023-04-02 We're measuring milliseconds, not microseconds
2023-04-04 Only use wavetable for sin, calculate the rest
    But keep the python scripts around for now.
2023-04-04 Refactor LFO into a struct, and be explicit about optimizing
2023-04-20 Save and load calibration data in EEPROM
2023-04-21 Make ADSR use envelope shape tables
2023-04-21 ADSR now has 3 independent envelopes
    And remove println to save a bit of flash (preparing for gate 3 out as well)
2023-04-25 Remove the arduino Wire library, saving lots of flash
    Also removing MIDI, which we'll be able to code up ourselves much more
    flash-efficient.
    We're also disabling Wire deep inside the LCD library, hence the added
    UserSettings.h.
2023-04-27 Add ability to tweak ADSR
2023-04-27 Reduce ADSR code size by not inlining and reusing classes
2023-04-28 Add loading and saving of presets
2023-04-28 Implement phase and range controls for LFO
2023-04-30 Add swing control to LFO
2023-05-03 Bring back Wire, since we need it for I2C speed
2023-05-03 Switch to lcdgfx' own TWI implementation, which is smaller
    This knocks a few kB off the byte size again.
2023-05-04 Reimplement MIDI module, refactor LFO to save flash
    and we're back to 10% free :)
2023-05-07 Add gate 3 to LFO, fix some of LFO's swing
    Swing on 3x still isn't working (since 3x doesn't divide well)
2023-05-08 Add probability to LFO
2023-05-09 Fix swing, prob and slop working nicely together
2023-05-10 Remove phase argument for waves
    Instead, calculate the phase directly inside the LFO.
2023-05-10 Add PWM to all waves
2023-05-15 Small refactorings, add in sequencer
2023-05-17 Add missing CPP file
2023-06-17 Fix the pinout of the offset POTs so right is plus
    These were reversed (it's an inverting amplifier) in the original
    design. Also added a marking to the board.
2023-06-17 Removing old backups
2023-06-17 Add mounting holes to power board
    And an extra trace connecting the AUX tracks (even though we're not
    using them now)
2024-06-14 Saving latest changes
2024-12-13 General upgrade of in-progress knobs
2024-12-13 Add PT-2399 delay
2024-12-13 Updated generated pictures
2024-12-14 Fixed feedback orientation (pin 1 should point low)
2024-12-14 Fixed up pinout of dry/wet as well
2024-12-16 Adjust layout so components can be folded over
2024-12-18 Small updates for delay while ordering first prototype
2024-12-18 Apply rev1 fixes to AS3340 VCO
2024-12-18 Update README and add a picture
2024-12-18 Apply fixes for DualMixer rev1 module
